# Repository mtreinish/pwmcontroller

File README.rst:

PWM Controller
==============

This repository contains the hardware design files (for use with KiCad) that
will create a PWM controller board. The intent here is to plug this in between
a motherboard 4-pin fan header and a powered fan splitter, like the Silverstone
CPF04 or Swiftech 8W-PWM-SPL-ST. The pwm signal is generated by the 555 timer
on the board and adjusted with the on pcb potentiometer, 12v fan power from
the motherboard is used solely for the DC/DC converter and 555 timer. No power
pins are connected on the output fan header.

A write up documenting this project's development can be found here:

https://blog.kortar.org/?p=437

.. image:: https://raw.githubusercontent.com/mtreinish/pwmcontroller/master/pwmcontroller.png

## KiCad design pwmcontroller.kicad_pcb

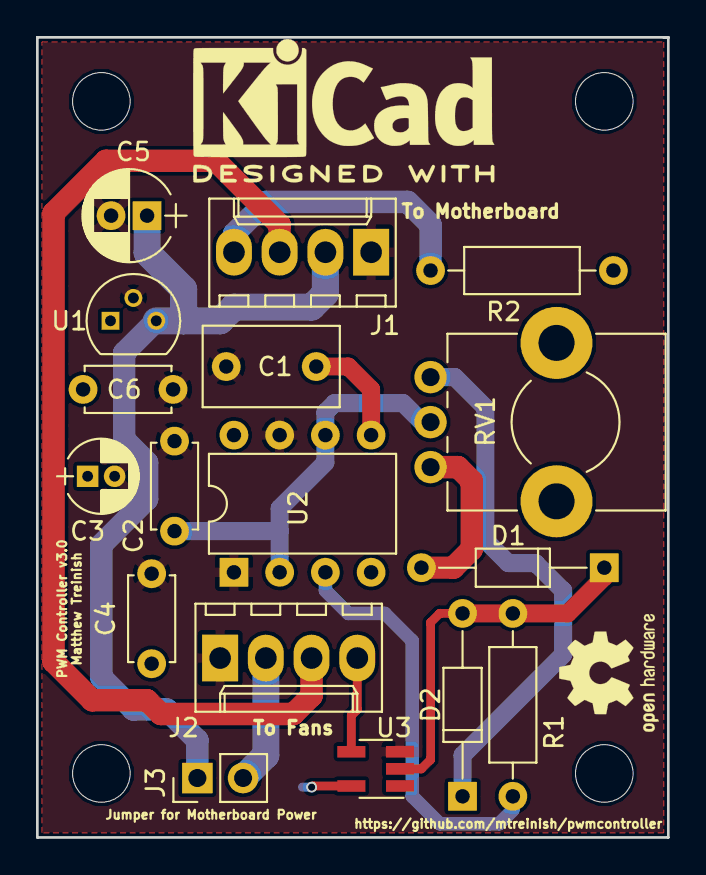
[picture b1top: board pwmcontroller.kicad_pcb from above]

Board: 2 copper layers, 35.1 x 44.5 mm, 17 parts (0 on the bottom side), 13 nets.

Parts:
C1: .01uF; C_Disc_D7.5mm_W4.4mm_P5.00mm
C2: 470pF; C_Disc_D4.7mm_W2.5mm_P5.00mm
C3: 10uF; CP_Radial_D4.0mm_P1.50mm
C4, C6: .1uF; C_Disc_D4.7mm_W2.5mm_P5.00mm
C5: .33uF; CP_Radial_D5.0mm_P2.00mm
D1, D2: 1N4148; D_DO-35_SOD27_P10.16mm_Horizontal
J1, J2: CONN_01X04; Molex_KK-6410-04_04x2.54mm_Straight
J3: Conn_01x02_Male; Socket_Strip_Straight_1x02_Pitch2.54mm
R1: 1K; R_Axial_DIN0207_L6.3mm_D2.5mm_P10.16mm_Horizontal
R2: 4.7K; R_Axial_DIN0207_L6.3mm_D2.5mm_P10.16mm_Horizontal
RV1: 100k; Potentiometer_Bourns_PTV09A-1_Horizontal
U1: MC78L05_TO92; TO-92_Molded_Narrow
U2: NE555; DIP-8_W7.62mm
U3: 74AHC1G14; SOT-23-5_HandSoldering

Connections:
+12V: C5.1, J1.2, J3.1, U1.3
/12V_OUT: J2.2, J3.2
/FAN_RPM: J1.3, J2.3
/PWM_OUT: D1.1, D2.2, R1.1, U3.2
/TRIG: C2.1, RV1.2, U2.2, U2.6
GND: C1.2, C2.2, C3.2, C4.2, C5.2, C6.2, J1.1, J2.1, U1.2, U2.1, U2.7, U3.3
unnamed: C1.1, U2.5
unnamed: D1.2, RV1.1
unnamed: D2.1, RV1.3
unnamed: J1.4, R2.2
unnamed: J2.4, U3.4
unnamed: R1.2, U2.3
VCC: C3.1, C4.1, C6.1, R2.1, U1.1, U2.4, U2.8, U3.5

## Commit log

2017-09-19 Add license file
2017-09-19 Fix component values
2017-09-24 Remove mounting hole silkscreen label
2017-09-24 Shrink PCB to smaller dimensions
2017-09-24 Add Silkscreen description on Board
2017-09-24 Move mouting holes in slightly
2017-09-24 Remove extra labels
2017-09-24 Mark output power pin as not onnected
2017-09-24 Fix isolated C3 ground pin on PCB
2017-09-26 Add a BOM
    This commit adds a Bill of Materials for the components used to
    construct the pwm controller.
2017-09-26 Switch mouser links to mouser part numbers
    The links to mouser were included for convenience, but it made the
    spreadsheet too wide. This commit switches it to use the mouser part
    number instead so they can easily be searched for on mouser.
2017-09-26 Add BOM pdf file
    The ods file doesn't render on github, so this commit adds a pdf too
    for convenient web viewing of the BOM.
2017-09-27 Add github link to PCB silkscreen
2017-10-01 Change C2 to 470pF
    After doing some breadboard testing the carrier frequency of the PWM
    signal was too low at only ~12kHz to ~14kHz. The PWM fan spec says this
    needs to be nominally 25kHz with a range of 21kHz to 28kHz. By
    decreasing the capacitance of the C2 to 470pF from 680pF this should
    adjust the frequency to be in this range. Next time I'll do the
    arithmetic before ordering parts.
2017-10-02 Rearrange device references for legibility
2017-10-02 Move around value labels for clarity
    This commit moves around the value text to make it a bit easier to read.
    While this isn't on an output layer it was a bit cluttered and difficult
    to read while working on the PCB layout.
2017-10-14 Add fan header labels
2017-12-29 Add Schmitt Trigger Output Buffer
    This commit adds a schmitt trigger output buffer to clean up the output
    signal.
2018-01-05 Add PCB image to README
2018-01-09 Fix floating output ground
2018-01-09 Update the README
    This commit adds a link to the blog post documenting the project's
    development.
2019-03-23 Pivot to revision 3 of the design
